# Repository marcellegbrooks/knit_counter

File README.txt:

Knit Stitch Counter

Marcelle Brooks
May 2024

Using buttons, a gyroscope, LEDs, a buzzer, a pressure sensor and an OLED screen,
this device is meant as a tool to aid knitters. It can keep track of the amount 
of stitches knit and record a pattern for the user so that the user can knit freely 
without counting. 

In the folder, you can find the circuit schematic and the pcb designs as well as
the 3D model used as a case to wear the board on your writs. 

The Arduino code programs an SAMD21 microchip.

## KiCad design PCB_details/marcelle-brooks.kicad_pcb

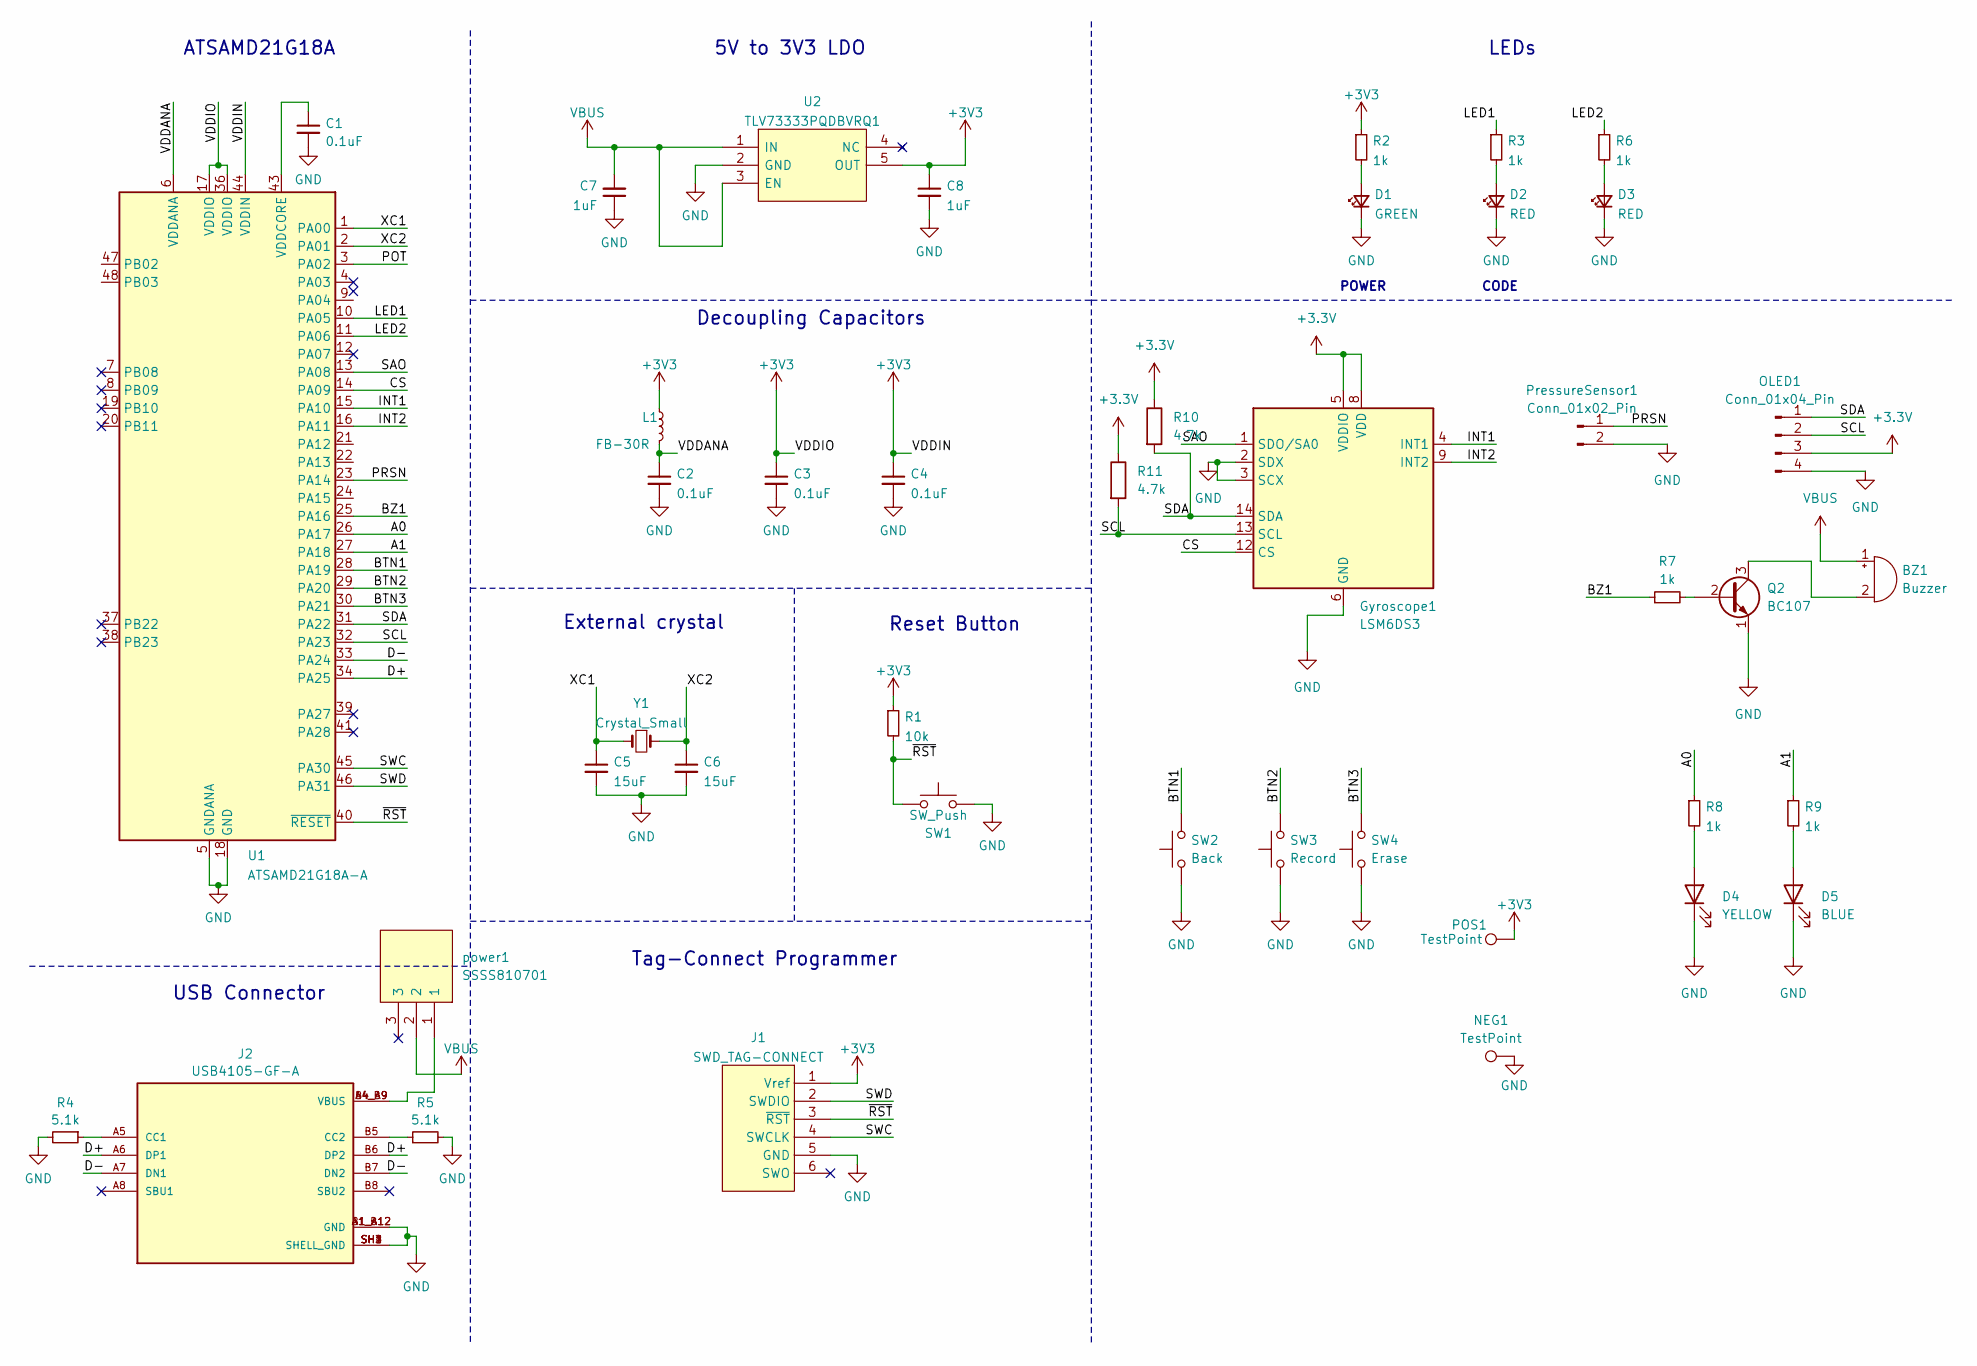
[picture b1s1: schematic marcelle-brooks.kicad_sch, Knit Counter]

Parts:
BZ1: Buzzer; Buzzer_Murata_PKMCS0909E
C1, C2, C3, C4: 0.1uF; C_0603_1608Metric_Pad1.08x0.95mm_HandSolder
C5, C6: 15uF; C_0603_1608Metric_Pad1.08x0.95mm_HandSolder
C7, C8: 1uF; C_0603_1608Metric_Pad1.08x0.95mm_HandSolder
D1: GREEN; LED_0603_1608Metric_Pad1.05x0.95mm_HandSolder
D2, D3: RED; LED_0603_1608Metric_Pad1.05x0.95mm_HandSolder
D4: YELLOW; LED_0805_2012Metric_Pad1.15x1.40mm_HandSolder; Part number LS R976-NR-1
D5: BLUE; LED_0805_2012Metric_Pad1.15x1.40mm_HandSolder; Part number LG R971-KN-1
Gyroscope1: LSM6DS3; LGA-14_3x2.5mm_P0.5mm_LayoutBorder3x4y
J1: SWD_TAG-CONNECT; Tag-Connect_TC2030-IDC-FP_2x03_P1.27mm_Vertical
J2: USB4105-GF-A; GCT_USB4105-GF-A
L1: FB-30R; L_0603_1608Metric_Pad1.05x0.95mm_HandSolder
NEG1: TestPoint; TestPoint_Pad_1.0x1.0mm
OLED1: Conn_01x04_Pin; PinHeader_1x04_P2.54mm_Vertical
POS1: TestPoint; TestPoint_Pad_1.0x1.0mm
PressureSensor1: Conn_01x02_Pin; PinHeader_1x02_P2.54mm_Vertical
Q2: BC107; SOT-23-3
R1: 10k; R_0603_1608Metric_Pad0.98x0.95mm_HandSolder
R2, R3, R6, R7, R8, R9: 1k; R_0603_1608Metric_Pad0.98x0.95mm_HandSolder
R4, R5: 5.1k; R_0603_1608Metric_Pad0.98x0.95mm_HandSolder
R10, R11: 4.7k; R_0603_1608Metric_Pad0.98x0.95mm_HandSolder
SW1: SW_Push; SW_SPST_TL3305A
SW2: Back; SW_SPST_TL3305A
SW3: Record; SW_SPST_TL3305A
SW4: Erase; SW_SPST_TL3305A
U1: ATSAMD21G18A-A; TQFP-48_7x7mm_P0.5mm
U2: TLV73333PQDBVRQ1; SOT95P280X145-5N; Mouser Part Number 595-TLV73333PQDBVRQ1
Y1: Crystal_Small; Crystal_SMD_3215-2Pin_3.2x1.5mm
power1: SSSS810701

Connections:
+3.3V: Gyroscope1.5 (VDDIO), Gyroscope1.8 (VDD), OLED1.3, R10.1, R11.1
+3V3: C3.1, C4.1, C8.1, J1.1 (Vref), L1.1, POS1.1, R1.1, R2.1, U1.17 (VDDIO), U1.36 (VDDIO), U1.44 (VDDIN), U2.5 (OUT)
/A0: R8.1, U1.26 (PA17)
/A1: R9.1, U1.27 (PA18)
/BTN1: SW2.2, U1.28 (PA19)
/BTN2: SW3.2, U1.29 (PA20)
/BTN3: SW4.2, U1.30 (PA21)
/BZ1: R7.1, U1.25 (PA16)
/CS: Gyroscope1.12 (CS), U1.14 (PA09)
/D+: J2.A6 (DP1), J2.B6 (DP2), U1.34 (PA25)
/D-: J2.A7 (DN1), J2.B7 (DN2), U1.33 (PA24)
/INT1: Gyroscope1.4 (INT1), U1.15 (PA10)
/INT2: Gyroscope1.9 (INT2), U1.16 (PA11)
/LED1: R3.1, U1.10 (PA05)
/LED2: R6.1, U1.11 (PA06)
/POT: U1.3 (PA02)
/PRSN: PressureSensor1.1, U1.23 (PA14)
/SAO: Gyroscope1.1 (SDO/SA0), U1.13 (PA08)
/SCL: Gyroscope1.13 (SCL), OLED1.2, R11.2, U1.32 (PA23)
/SDA: Gyroscope1.14 (SDA), OLED1.1, R10.2, U1.31 (PA22)
/SWC: J1.4 (SWCLK), U1.45 (PA30)
/SWD: J1.2 (SWDIO), U1.46 (PA31)
/VDDANA: C2.1, L1.2, U1.6 (VDDANA)
/XC1: C5.1, U1.1 (PA00), Y1.2
/XC2: C6.1, U1.2 (PA01), Y1.1
/~RST: J1.3 (~RST), R1.2, SW1.1, U1.40 (~RESET)
GND: C1.2, C2.2, C3.2, C4.2, C5.2, C6.2, C7.1, C8.2, D1.1 (K), D2.1 (K), D3.1 (K), D4.1 (K), D5.1 (K), Gyroscope1.2 (SDX), Gyroscope1.3 (SCX), Gyroscope1.6 (GND), Gyroscope1.7 (GND), J1.5 (GND), J2.A1_B12 (GND), J2.B1_A12 (GND), J2.SH1 (SHELL_GND), J2.SH2 (SHELL_GND), J2.SH3 (SHELL_GND), J2.SH4 (SHELL_GND), NEG1.1, OLED1.4, PressureSensor1.2, Q2.1 (E), R4.2, R5.2, SW1.2, SW2.1, SW3.1, SW4.1, U1.5 (GNDANA), U1.18 (GND), U1.35 (GND), U1.42 (GND), U2.2 (GND)
unnamed: BZ1.2 (-), Q2.3 (C)
unnamed: D1.2 (A), R2.2
unnamed: D2.2 (A), R3.2
unnamed: D3.2 (A), R6.2
unnamed: D4.2 (A), R8.2
unnamed: D5.2 (A), R9.2
unnamed: J2.A5 (CC1), R4.1
unnamed: J2.B5 (CC2), R5.1
unnamed: J2.A4_B9 (VBUS), J2.B4_A9 (VBUS), power1.1
unnamed: Q2.2 (B), R7.2
unnamed: C1.1, U1.43 (VDDCORE)
VBUS: BZ1.1 (+), C7.2, U2.1 (IN), U2.3 (EN), power1.2

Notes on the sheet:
5V to 3V3 LDO
External crystal
Tag-Connect Programmer
Decoupling Capacitors
CODE
LEDs
POWER
USB Connector
ATSAMD21G18A
Reset Button

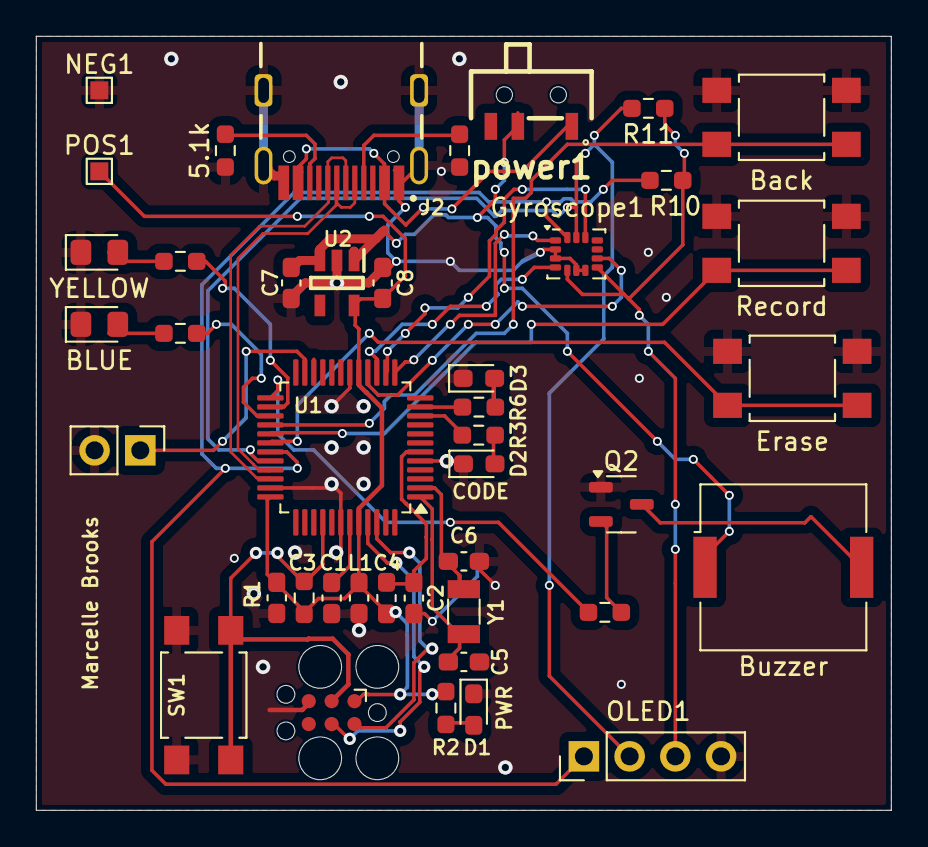
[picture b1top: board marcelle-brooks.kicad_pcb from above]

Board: 2 copper layers, 47.5 x 43.0 mm, 42 parts (0 on the bottom side), 38 nets.

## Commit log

2024-06-28 knit counter
2024-07-02 project photo commit
